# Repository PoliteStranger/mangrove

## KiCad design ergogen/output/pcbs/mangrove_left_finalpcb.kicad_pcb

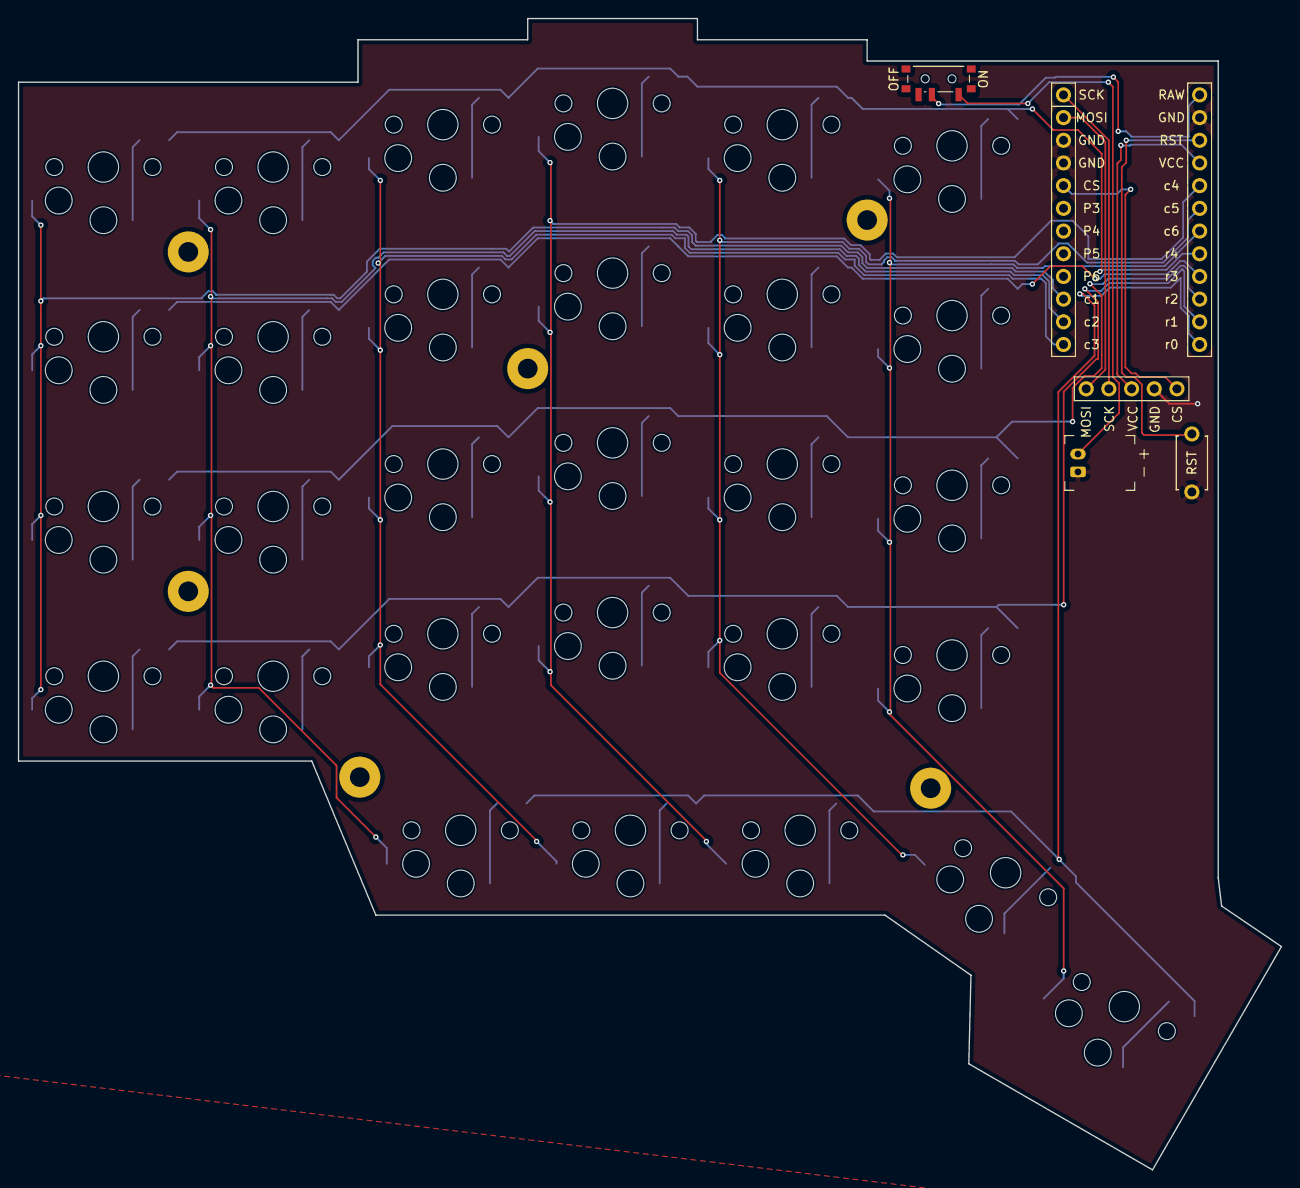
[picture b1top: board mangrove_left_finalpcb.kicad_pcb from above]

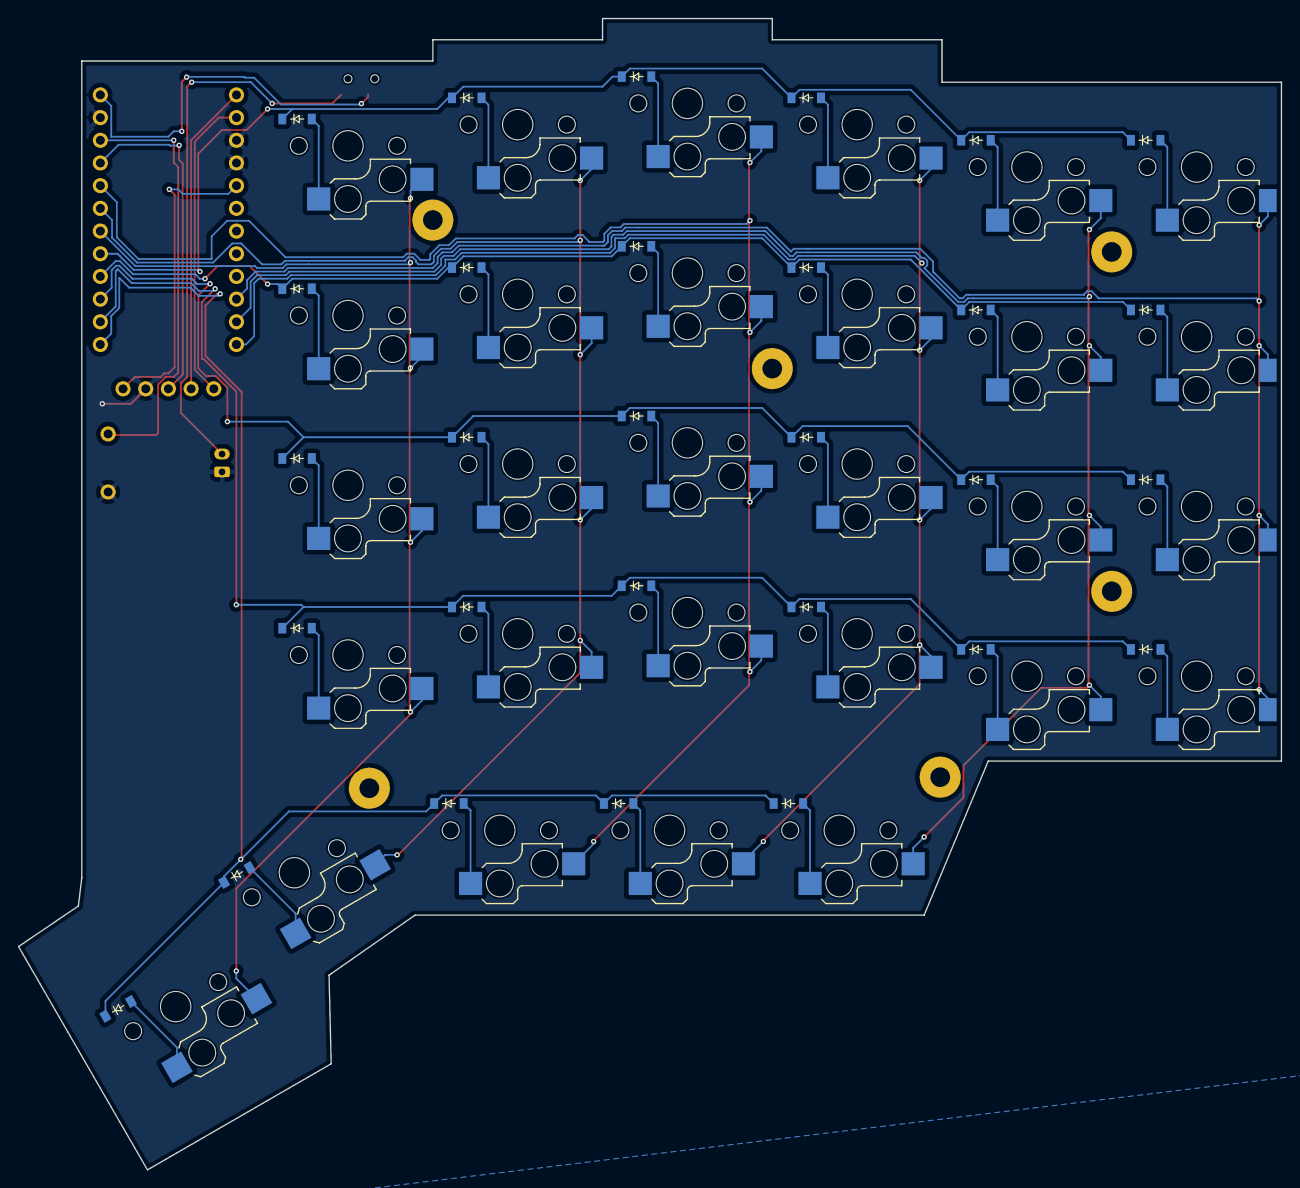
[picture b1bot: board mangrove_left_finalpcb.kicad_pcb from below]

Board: 2 copper layers, 141.4 x 128.9 mm, 69 parts (58 on the bottom side), 48 nets.

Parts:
D1, D2, D3, D4, D5, D6, D7, D8, D9, D10, D11, D12, D13, D14, D15, D16, D17, D18, D19, D20, D21, D22, D23, D24, D25, D26, D27, D28, D29: diode_tht_sod123
DISP1: display_nice_view
JST1: battery_connector_jst_ph_2
MCU1: mcu_nice_nano
MH1, MH2, MH3, MH4, MH5, MH6: mounting_hole_npth
PWR1: power_switch_smd_side
RST1: reset_switch_tht_top
S1, S2, S3, S4, S5, S6, S7, S8, S9, S10, S11, S12, S13, S14, S15, S16, S17, S18, S19, S20, S21, S22, S23, S24, S25, S26, S27, S28, S29: switch_choc_v1_v2

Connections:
BAT_P: JST1.2, PWR1.1
CS: DISP1.5, MCU1.20
GND: DISP1.4, JST1.1, MCU1.2, MCU1.21, MCU1.22, RST1.2
MOSI: DISP1.1, MCU1.23
RAW: MCU1.1, PWR1.2
RST: MCU1.3, RST1.1
SCK: DISP1.2, MCU1.24
VCC: DISP1.3, MCU1.4
c1: MCU1.15, S24.2, S25.2, S26.2, S27.2
c1_r1: D1.2, S24.1
c1_r2: D2.2, S25.1
c1_r3: D3.2, S26.1
c1_r4: D4.2, S27.1
c2: MCU1.14, S1.2, S2.2, S3.2, S4.2, S21.2
c2_r0: D25.2, S21.1
c2_r1: D5.2, S1.1
c2_r2: D6.2, S2.1
c2_r3: D7.2, S3.1
c2_r4: D8.2, S4.1
c3: MCU1.13, S5.2, S6.2, S7.2, S8.2, S22.2
c3_r0: D26.2, S22.1
c3_r1: D9.2, S5.1
c3_r2: D10.2, S6.1
c3_r3: D11.2, S7.1
c3_r4: D12.2, S8.1
c4: MCU1.5, S9.2, S10.2, S11.2, S12.2, S23.2
c4_r0: D27.2, S23.1
c4_r1: D13.2, S9.1
c4_r2: D14.2, S10.1
c4_r3: D15.2, S11.1
c4_r4: D16.2, S12.1
c5: MCU1.6, S13.2, S14.2, S15.2, S16.2, S28.2
c5_r0: D28.2, S28.1
c5_r1: D17.2, S13.1
c5_r2: D18.2, S14.1
c5_r3: D19.2, S15.1
c5_r4: D20.2, S16.1
c6: MCU1.7, S17.2, S18.2, S19.2, S20.2, S29.2
c6_r0: D29.2, S29.1
c6_r1: D21.2, S17.1
c6_r2: D22.2, S18.1
c6_r3: D23.2, S19.1
c6_r4: D24.2, S20.1
r0: D25.1, D26.1, D27.1, D28.1, D29.1, MCU1.12
r1: D1.1, D5.1, D9.1, D13.1, D17.1, D21.1, MCU1.11
r2: D2.1, D6.1, D10.1, D14.1, D18.1, D22.1, MCU1.10
r3: D3.1, D7.1, D11.1, D15.1, D19.1, D23.1, MCU1.9
r4: D4.1, D8.1, D12.1, D16.1, D20.1, D24.1, MCU1.8

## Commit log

2026-01-03 readme
2026-01-03 commited config
2026-01-04 added ergogen and kicad
2026-01-05 split pcb
2026-01-29 fixed some distances
2026-01-30 finished design
